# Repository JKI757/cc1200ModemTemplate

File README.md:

Very basic layout, based loosely on TI's EMK board, with component LCSC numbers cribbed from the M17 project's "Exploded M17" project.  matching network should be loosely around 440 mhz but you'll want to customize for your application.

I'm not an RF engineer or PCB layout expert, so use at your own risk.  Pull requests welcome if you know better than I do on anything here.  

License is unlicense, use it how you want to, I don't consider this to be intellectual property, it's just a combination of parts following datasheets and sample layouts.

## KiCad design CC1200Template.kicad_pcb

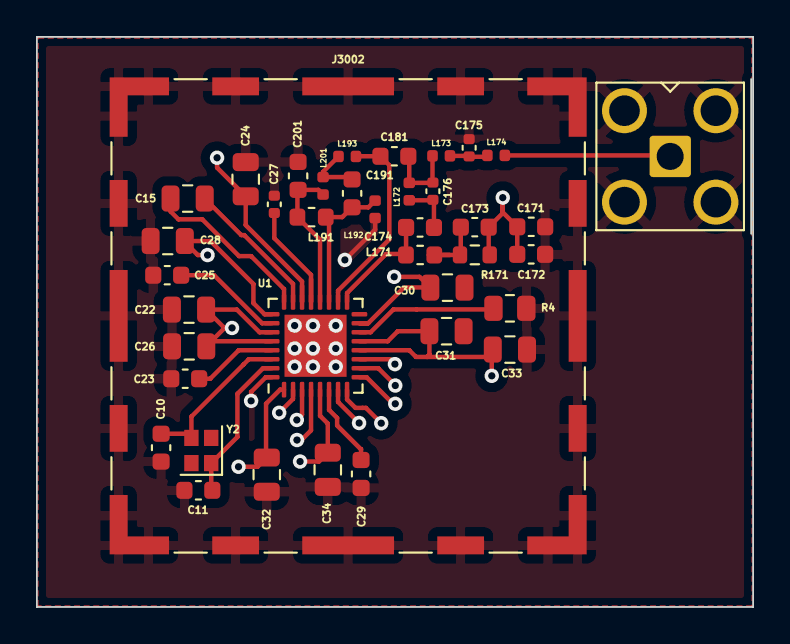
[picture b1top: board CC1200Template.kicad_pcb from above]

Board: 4 copper layers, 39.8 x 31.7 mm, 39 parts (0 on the bottom side), 21 nets.

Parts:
C10, C11: 12p; C_0603_1608Metric
C15: 1.5n; C_0805_2012Metric
C22, C24, C26, C28, C30, C31, C32, C33, C34: 47n; C_0805_2012Metric
C23, C25: 47n; C_0603_1608Metric
C27: 10n; C_0402_1005Metric
C29: 220n; C_0603_1608Metric
C171: 10n; C_0603_1608Metric
C172: 100p; C_0603_1608Metric
C173: 56p; C_0603_1608Metric
C174: 39p; C_0603_1608Metric
C175: 6.2p; C_0402_1005Metric
C176: 2.2p; C_0402_1005Metric
C181, C191, C201: 5.1p; C_0603_1608Metric
J1: Conn_Coaxial; HJ_Tech_SMA_Horizontal_Board_Edge_RF
J3002: RFShield_OnePiece; Wuerth_36103255_25x25mm
L171, L191: 56n; L_0603_1608Metric
L172, L193: 15n; L_0402_1005Metric
L173: 43n; L_0402_1005Metric
L174: 22n; L_0402_1005Metric
L192, L201: 27n; L_0402_1005Metric
R4: 56k; R_0805_2012Metric
R171: 18; R_0603_1608Metric
U1: CC1200; QFN-32-1EP_5x5mm_P0.5mm_EP3.45x3.45mm
Y2: 40 MHz; Crystal_SMD_2016-4Pin_2.0x1.6mm

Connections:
+3V3: C22.1, C24.1, C26.1, C28.1, C30.1, C31.1, C32.1, C33.1, C34.1, C171.1, C172.1, C173.1, R171.1, U1.1 (VDD_GUARD), U1.5 (DVDD), U1.12 (DVDD), U1.13 (AVDD_IF), U1.15 (AVDD_RF), U1.22 (AVDD_SYNTH1), U1.25 (AVDD_PFD_CHP), U1.27 (AVDD_SYNTH2), U1.28 (AVDD_XOSC)
GND: C10.1, C11.2, C22.2, C23.2, C24.2, C25.2, C26.2, C27.2, C28.2, C29.2, C30.2, C31.2, C32.2, C33.2, C34.2, C171.2, C172.2, C175.2, C201.2, J1.2 (Ext), J3002.1 (Shield), L192.1, R4.2, U1.32 (EXT_XOSC), U1.33 (GND_EP)
unnamed: C10.2, U1.30 (XOSC_Q1), Y2.3
unnamed: C11.1, U1.31 (XOSC_Q2), Y2.1
unnamed: C15.1, U1.23 (LPF0)
unnamed: C15.2, U1.24 (LPF1)
unnamed: C23.1, U1.29 (DCPL_XOSC)
unnamed: C25.1, U1.26 (DCPL_PFD_CHP)
unnamed: C27.1, U1.21 (DCPL_VCO)
unnamed: C29.1, U1.6 (DCPL)
unnamed: C173.2, L171.2, R171.2
unnamed: C174.1, C176.2, L172.1
unnamed: C175.1, L173.2, L174.1
unnamed: C176.1, C181.1, L172.2, L173.1
unnamed: C181.2, L193.2, U1.18 (TRX_SW)
unnamed: C191.1, L191.1, L192.2, U1.19 (LNA_P)
unnamed: C191.2, L193.1, L201.1
unnamed: C201.1, L191.2, L201.2, U1.20 (LNA_N)
unnamed: J1.1 (In), L174.2
unnamed: R4.1, U1.14 (RBIAS)
unnamed: C174.2, L171.1, U1.17 (PA)

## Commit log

2022-11-25 fix clearance issues & errors in footprints
2022-11-26 fix clearance issues & errors in footprints and add vias for ground and add ground and vcc pours
2022-12-24 add readme
